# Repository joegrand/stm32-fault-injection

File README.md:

# STM32F2 / F4 Fault Injection

Authors: [Joe Grand](https://joegrand.com) and [Lennert Wouters](https://x.com/lennertwo)

The [STMicroelectronics](https://www.st.com/) STM32 family of microcontrollers is deployed in billions of embedded systems, making them desirable, high-value targets. In particular, the [STM32F2](https://www.st.com/en/microcontrollers-microprocessors/stm32f2-series.html) and [STM32F4](https://www.st.com/en/microcontrollers-microprocessors/stm32f4-series.html) have been heavily scrutinized due to their use in popular cryptocurrency hardware wallets like the [Trezor One](https://trezor.io/trezor-model-one), [Trezor Model T](https://trezor.io/trezor-model-t), and [KeepKey](https://keepkey.com/). Previous research has shown that fault injection can bypass protection mechanisms and enable flash memory extraction. However, those techniques can lead to device corruption or permanent loss of data.

Our work comprises three years of refining and extending these attacks into a more repeatable and reliable process for extracting protected flash memory from STM32F2 and STM32F4 devices, including:

* Characterizing fault injection parameters using EMFI (Electromagnetic Fault Injection) and VFI (Voltage Fault Injection)
* Downgrading from STM32 RDP level 2 to level 1 using EMFI and VFI
    * We found that the STM32F2 is susceptible to a very early downgrade using EMFI
* Bootloader command glitching to safely extract flash memory contents
* A new strategy that combines two known attacks: Our RDP level 2 to level 1 downgrade and the [Flash Patch and Breakpoint (FPB)](#flash-patch-and-breakpoint-fpb) attack
    * This allows us to extract the full flash contents using only two glitches

This repository accompanies our [REcon 2026](https://recon.cx/2026/en/index.html) presentation "[Failure Is Not an Option: A Reliable Process to Exploit STM32F2/F4 Microcontrollers](https://www.youtube.com/watch?v=4LahQG09NzI)" and contains the following:

* [Jupyter notebooks](https://github.com/joegrand/stm32-fault-injection/tree/main/notebooks) and associated wrappers for the ChipWhisperer and STM32 bootloader
* [Source code](https://github.com/joegrand/stm32-fault-injection/tree/main/source) for characterization test code and FPB payload
* [Hardware designs](https://github.com/joegrand/stm32-fault-injection/tree/main/hardware) for evaluation and attack
* [Slides](https://github.com/joegrand/stm32-fault-injection/tree/main/slides)

This project has been developed and tested for the STM32F205 and STM32F427. It is unsupported, but for public discussion you can submit an [Issue](https://github.com/joegrand/stm32-fault-injection/issues) or visit [Joe Grand's Discord server](https://discord.com/invite/wud8KnF2Gm).

## Requirements

### Hardware

* [ChipWhisperer-Husky](https://www.newae.com/products/nae-cwhusky)
* [NewAE CW308 UFO Board](https://rtfm.newae.com/Targets/CW308%20UFO/)
* [Segger J-Link](https://www.segger.com/products/debug-probes/j-link/)
* [ChipSHOUTER](https://www.newae.com/products/nae-cw520) (Optional)
* CNC Milling Machine w/ [GRBL](https://github.com/gnea/grbl) controller (for example, [3018 Pro-MAX](https://www.amazon.com/LUNYEE-MAX-All-Metal-Switches-Emergency-Stop/dp/B0C6WQWX3R) w/ [Doesbot](https://www.amazon.com/gp/product/B0C625ZCN7/)) (Optional)
* Target device: [STM32F2](https://www.st.com/en/microcontrollers-microprocessors/stm32f2-series.html) or [STM32F4](https://www.st.com/en/microcontrollers-microprocessors/stm32f4-series.html) with socket/adapter board

### Software

To run the code, you will need Python 3 and some additional packages. Assuming you have Python 3 installed, you should be able to create a new virtual environment using the following instructions:

* Clone this repository: `git clone https://github.com/joegrand/stm32-fault-injection`
* Create a virtual environment: `cd stm32-fault-injection && python3 -m venv stm32_venv`
* Activate the virtual environment: `source ./stm32_venv/bin/activate`
* Update pip: `python -m pip install --upgrade pip`
* Install the required libraries: `python -m pip install -r requirements.txt`
* Install from source:
  * PyLink must include the [Add raw JTAG support #86](https://github.com/square/pylink/pull/86) pull request. This is not currently in their main repository, so it should be installed from source with this PR added locally.
  * You may want to [install the ChipWhisperer software from source](https://chipwhisperer.readthedocs.io/en/latest/installation.html) to get the latest version. This code has been developed and tested with v6.0.0.
* Start the Jupyter server: `cd notebooks && python -m jupyter notebook`

## Other Resources

### RDP Downgrade

* [wallet.fail](https://media.ccc.de/v/35c3-9563-wallet_fail) and [chip.fail](https://www.youtube.com/watch?v=CX71p_qcCxY)
* [Kraken Identifies Critical Flaw in Trezor Hardware Wallets](https://blog.kraken.com/post/3662/kraken-identifies-critical-flaw-in-trezor-hardware-wallets/)
* [Inside Kraken Security Labs: Flaw Found in Keepkey Crypto Hardware Wallet Part 1](https://blog.kraken.com/product/security/flaw-found-in-keepkey-crypto-hardware-wallet) and [Part 2](https://blog.kraken.com/product/security/flaw-found-in-keepkey-crypto-hardware-wallet-part-2)
* [Verifying Code Readout Protection Claims](https://circuitcellar.com/archive-article/verifying-code-readout-protection-claims/)
* [Shedding too much Light on a Microcontroller’s Firmware Protection](https://www.aisec.fraunhofer.de/en/FirmwareProtection.html)
* [SiliconToaster: A Cheap and Programmable EM Injector for Extracting Secrets](https://eprint.iacr.org/2020/1115.pdf)
* [Unlock the Door to my Secrets, but don’t Forget to Glitch](https://tches.iacr.org/index.php/TCHES/article/view/11422)
* [VoidStar Security FI Resources](https://github.com/voidstarsec/fi-resources/)
* [Microcontroller Exploits (Travis Goodspeed)](https://nostarch.com/microcontroller-exploits)

### Bootloader Read Memory Glitch

* [Shaping the Glitch: Optimizing Voltage Fault Injection Attacks](https://tches.iacr.org/index.php/TCHES/article/view/7390)
* [Read secure firmware from STM32F1xx flash using ChipWhisperer (Prog.World)](https://web.archive.org/web/20201021153452/https:/prog.world/read-secure-firmware-from-stm32f1xx-flash-using-chipwhisperer/)
* [Replicant (Wrongbaud)](https://github.com/wrongbaud/replicant)

### Flash Patch and Breakpoint (FPB)
* [One Exploit to Rule them All? On the Security of Drop-in Replacement and Counterfeit Microcontrollers](https://www.usenix.org/system/files/woot20-paper-obermaier.pdf)
* [STM32F1 Pico Pwner (CTXz)](https://github.com/CTXz/stm32f1-picopwner)
* [STM32F4 readout protection exploit (lolwheel)](https://github.com/lolwheel/stm32f4-rdp-workaround)

### Joe's Related Wallet Hacking Videos
* [How I hacked a hardware crypto wallet and recovered $2 million](https://www.youtube.com/watch?v=dT9y-KQbqi4)
* [$75,000,000 Crypto Wallet Bulk Hack](https://www.youtube.com/watch?v=MhJoJRqJ0Wc)
* [The Shocking Result of My $75 Million Bulk Hack](https://www.youtube.com/watch?v=TGmGiN5Pa48)

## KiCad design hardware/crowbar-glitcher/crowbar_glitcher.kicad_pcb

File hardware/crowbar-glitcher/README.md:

# Crowbar Glitcher

Designed by [Joe Grand](https://joegrand.com) and [Lennert Wouters](https://x.com/lennertwo)

Fault injection/glitching board with two different MOSFETs (IRF8736T and DMG2302UK). 

A front-end MOSFET driver circuit is used to drive the gates of the N-channel MOSFETs. The board also includes an on-board adjustable LDO linear regulator that can be used to power the target board.

Known issue: If you want to drive the MOSFETs (Q1 or Q2) directly, the MOSFET driver circuitry needs to be disabled. The intended method of setting JP1 to Bypass and removing the EN Driver jumper does not work and causes undesirable loading. To completely isolate the MOSFET driver circuitry, you can drive Q1 and Q2 directly from the Q Select jumper pins 1 or 3. Or, to use the SMA Pulse IN connector, remove R3, connect JP1 pin 2 to JP3 pin 2, and then select the desired MOSFET accordingly using the JP3 jumper.	 

Bare boards available through [OSH Park](https://oshpark.com/shared_projects/ijuNYtEx)

Distributed under a [Creative Commons Attribution 4.0 International](https://creativecommons.org/licenses/by/4.0/) license

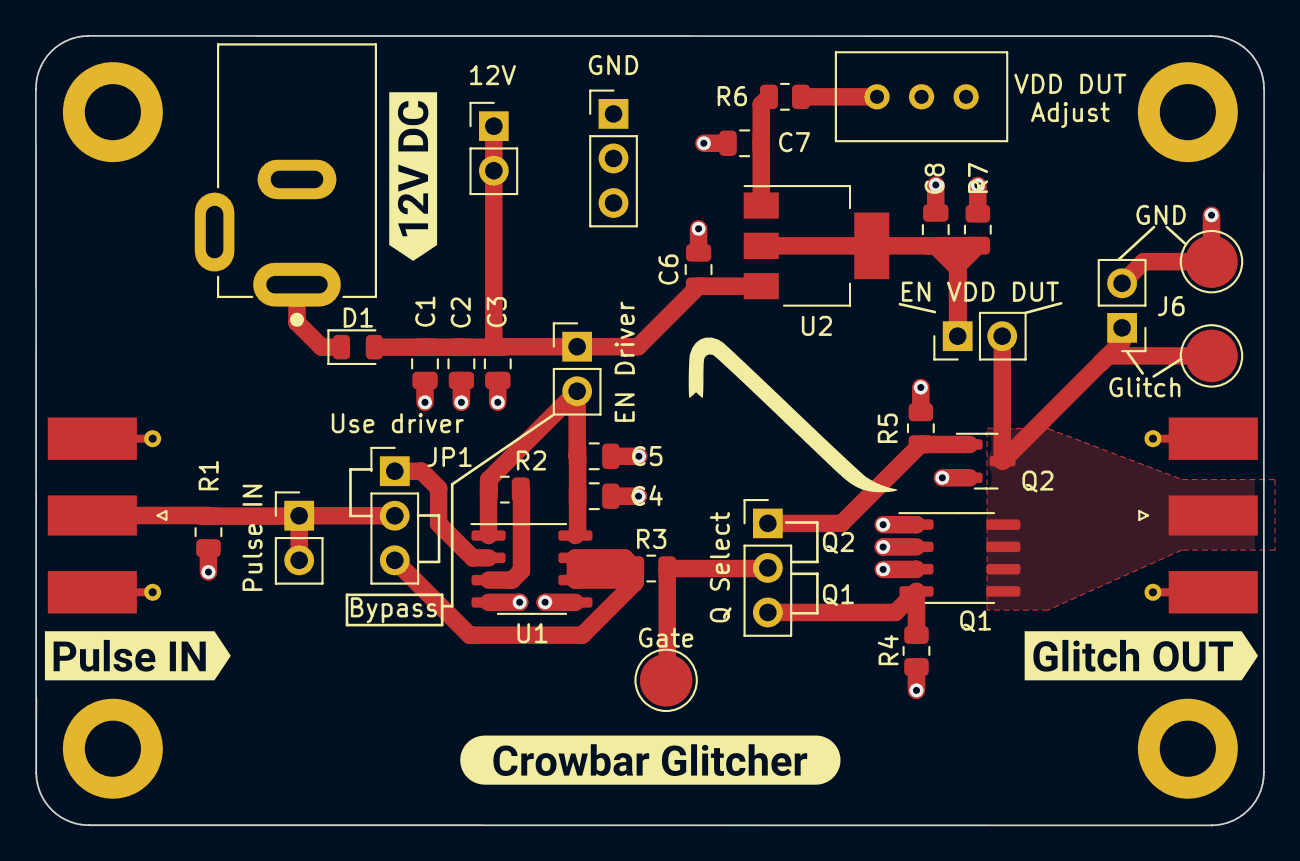
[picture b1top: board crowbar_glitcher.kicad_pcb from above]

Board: 2 copper layers, 70.0 x 45.0 mm, 43 parts (0 on the bottom side), 15 nets.

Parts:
C1: 22u; C_0805_2012Metric
C2, C4, C6: 1u; C_0805_2012Metric
C3, C5: 100n; C_0805_2012Metric
C7: 0.1u; C_0805_2012Metric
C8: 2.2u; C_0805_2012Metric
D1: DIODE; D_0805_2012Metric
GND: gnd_solder; TestPoint_Pad_D3.0mm
Gate: TP_GATE; TestPoint_Pad_D3.0mm
Glitch: glitch_solder; TestPoint_Pad_D3.0mm
H1, H2, H3, H4: MountingHole_Pad; MountingHole_3.2mm_M3_ISO7380_Pad
J1: Barrel_Jack_Switch; CUI_PJ-202A
J2: 12V_connector; PinHeader_1x02_P2.54mm_Vertical
J3: Pulse_input_SMA; SMA_Molex_73251-1153_EdgeMount_Horizontal
J4: pulse_in_connector; PinHeader_1x02_P2.54mm_Vertical
J5: GND_connector; PinHeader_1x03_P2.54mm_Vertical
J6: glitch_out_connector; PinHeader_1x02_P2.54mm_Vertical
J7: Glitch_SMA; SMA_Molex_73251-1153_EdgeMount_Horizontal
JP1: JP_driver_bypass; PinHeader_1x03_P2.54mm_Vertical
JP2: JP_driver_EN; PinHeader_1x02_P2.54mm_Vertical
JP3: JP_MOSFET_SEL; PinHeader_1x03_P2.54mm_Vertical
JP4: JP_LDO_EN; PinHeader_1x02_P2.54mm_Vertical
Q1: IRF7834/IRF7836; SOIC-8_3.9x4.9mm_P1.27mm
Q2: DMG2302UK; SOT-23
R1, R2, R7: DNP; R_0805_2012Metric
R3, R6: 0; R_0805_2012Metric
R4, R5: 10k; R_0805_2012Metric
RV1: 500k; Potentiometer_Bourns_3296W_Vertical
U1: MCP14A0602; SOIC-8_3.9x4.9mm_P1.27mm
U2: LT3082; SOT-223
kibuzzard-63C44E6F: G***; kibuzzard-63C44E6F
kibuzzard-63C44F7C: G***; kibuzzard-63C44F7C
kibuzzard-63C44F34: G***; kibuzzard-63C44F34
kibuzzard-63C571F5: G***; kibuzzard-63C571F5

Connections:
/12V: C1.1, C2.1, C3.1, C6.1, D1.2 (A), J2.1, J2.2, JP2.1, U2.3 (IN)
/V_target: Glitch.1, J6.1, J7.1 (In), JP4.2, Q1.5 (D), Q1.6 (D), Q1.7 (D), Q1.8 (D), Q2.3 (D)
GND: C1.2, C2.2, C3.2, C4.2, C5.2, C6.2, C7.2, C8.2, GND.1, J1.2, J3.2 (Ext), J5.1, J5.2, J5.3, J6.2, J7.2 (Ext), Q1.1 (S), Q1.2 (S), Q1.3 (S), Q2.2 (S), R1.2, R4.2, R5.2, R7.2, RV1.2, RV1.3, U1.4 (GND), U1.5 (GND)
unnamed: C4.1, C5.1, JP2.2, R2.2, U1.1 (VDD), U1.8 (VDD)
unnamed: C7.1, R6.2, U2.1 (SET)
unnamed: C8.1, JP4.1, R7.1, U2.2 (OUT), U2.4 (OUT)
unnamed: D1.1 (K), J1.1
unnamed: J3.1 (In), J4.1, J4.2, JP1.2, R1.1
unnamed: JP1.1, U1.2 (IN)
unnamed: JP1.3, R3.1, U1.6 (OUT), U1.7 (OUT)
unnamed: JP3.1, Q2.1 (G), R5.1
unnamed: Gate.1, JP3.2, R3.2
unnamed: JP3.3, Q1.4 (G), R4.1
unnamed: R2.1, U1.3 (EN)
unnamed: R6.1, RV1.1
